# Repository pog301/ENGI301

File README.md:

# ENGI301 
Repository for ENGI301 course work.

This has four folders:

1) assignment_03
   A small section for one of the class asignments. 
3) project_01
   Folder containing the content for the first class project - see the README within this folder
4) project_02
   Folder containing the content for the second class project - see the README within this folder
6) python
   Any other python files not within project_01 developed in this course. 

Disclaimer: This includes student work developed as part of a course. As such, some components might be missing or do not work as desired, and the quality is that of someone learning this for the first time. Additionally, a lot of the code was developed as part of the course or facilitated by the work done in the course. Thus, I take no responsibility for the use of any file, code or any other part within this repository.

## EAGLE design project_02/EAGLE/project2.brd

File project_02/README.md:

# Project 2

The goal of project 2 was to create a Printed Circuit Board (PCB) Design for an Etch-a-Sketch. The PCB contains the following components in the front of the board:
1) SPI screen to draw on
2) x2 potentiometers (one for moving in the x direction and the other one for moving in the y direction) 
3) x2 buttons (one for changing the color you draw with and another one for reseting the game)
4) x3 LEDs (one red, one blue and one green to display the drawing color)

The PCB also has the following in the back:
1) USB Port
2) PocketBeagle

Additionally, the subfolder for this project ("project_02") within this repository contains the following subfolders:
1) A subfolder named "EAGLE" with the Library, Schematics and Layout needed to build the PCB
2) A subfolder named "MFG" containing all of the manufacturing files for the PCB
3) A subfolder named "docs" with any other documents submitted to the course as part of this project

Disclaimer: This is student work developed as part of a course. As such, some components might be missing and the quality is that of someone learning this for the first time. Additionally, a lot of the content was developed as part of the course or facilitated by the work done in the course. Thus, I take no responsibility for the use of any part of the project. Also, my professor helped me throughout the process, so I might not know the answers to some of the questions.

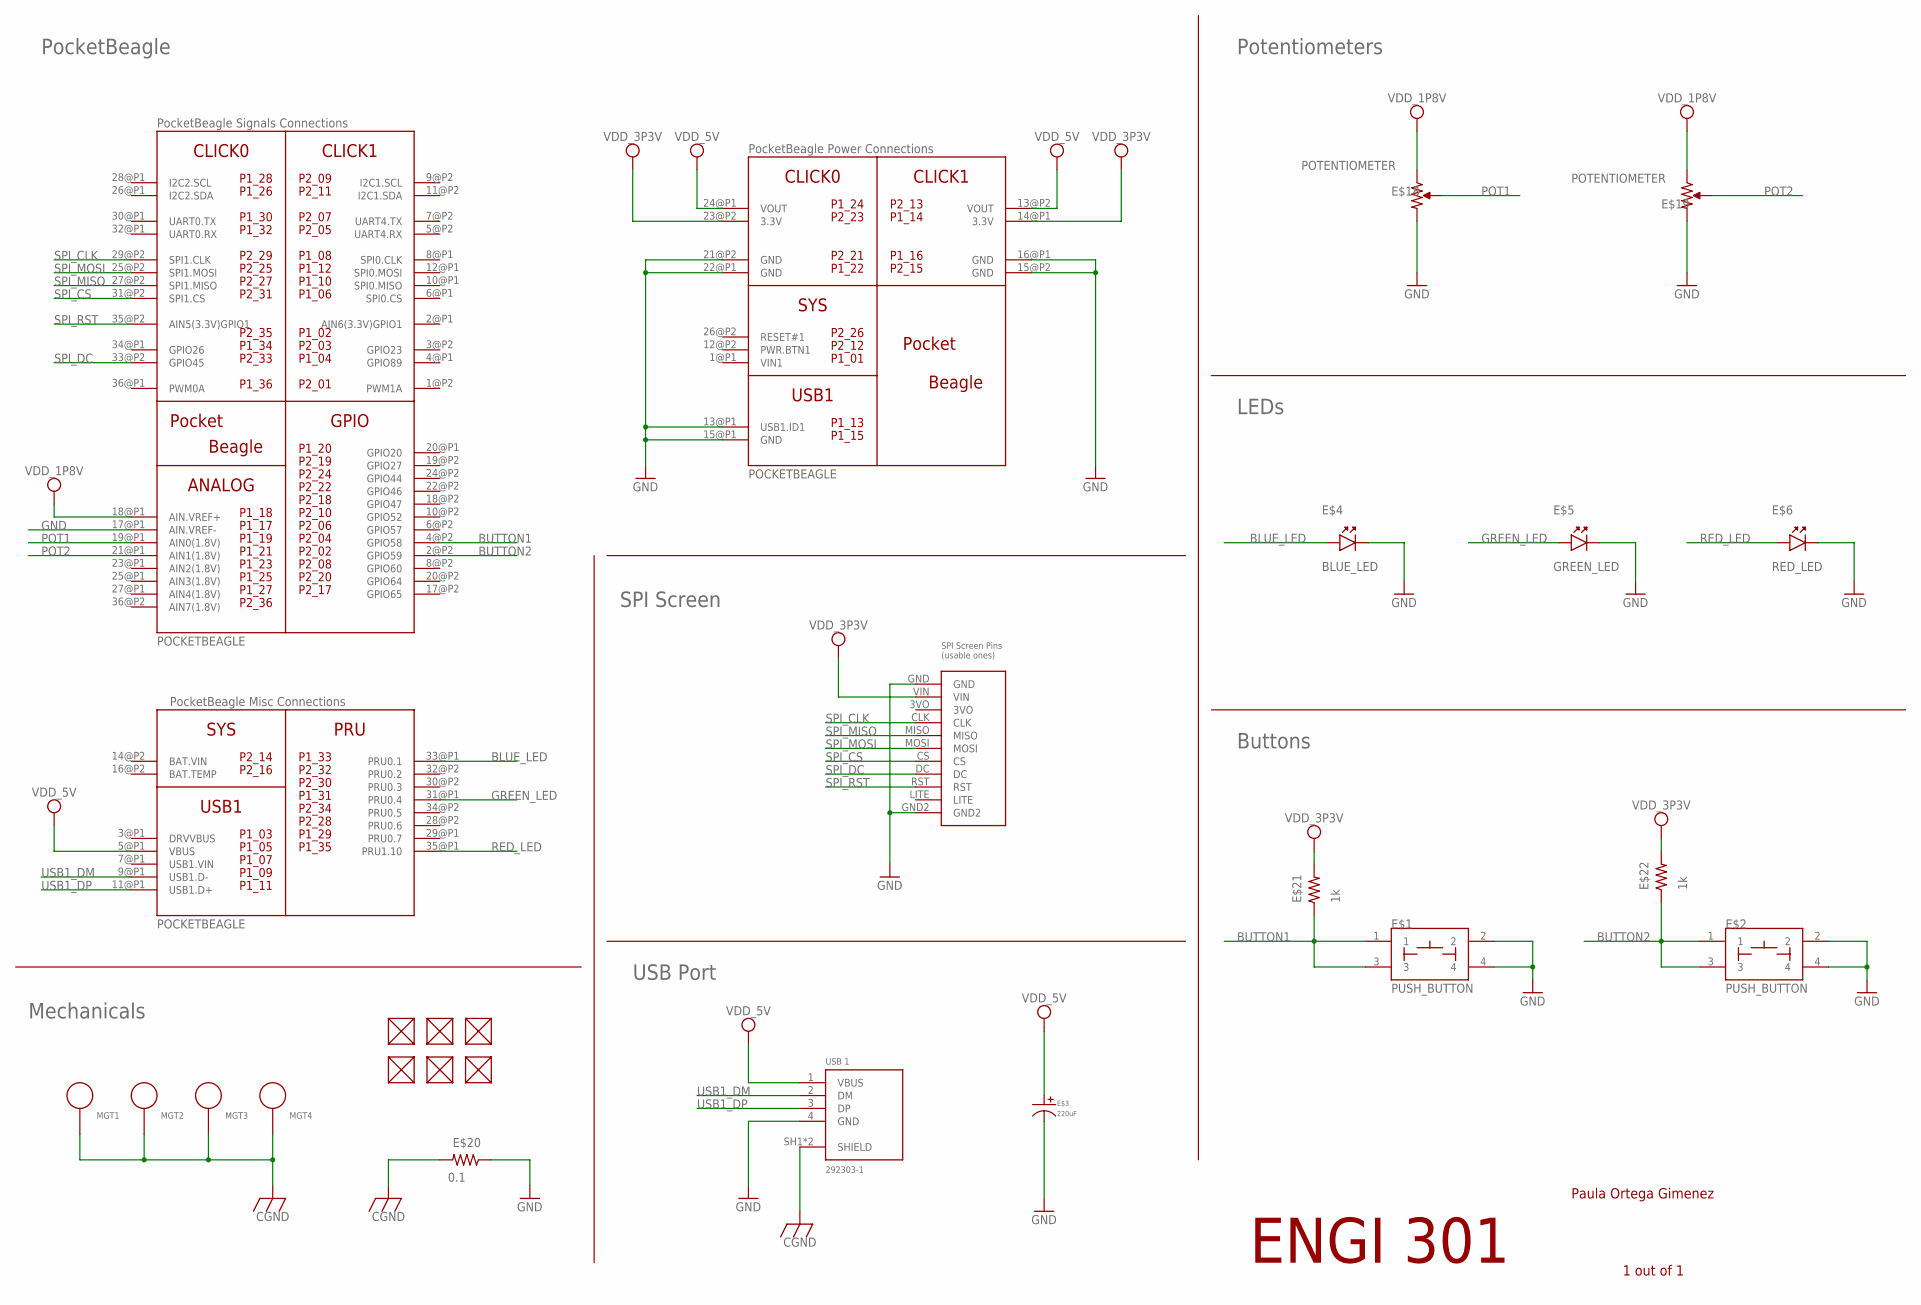
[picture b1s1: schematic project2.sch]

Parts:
E$1, E$2: PUSH_BUTTON; BUTTON_12.5MM
E$3: 220uF; CP10MM
E$4: BLUE_LED; EIA-STD
E$5: GREEN_LED; EIA-STD
E$6: RED_LED; EIA-STD
E$18, E$19: POTENTIOMETER; POT-PO90S
E$20: 0.1; R0805
E$21, E$22: 1k; R0805
E$24: 292303-1; TE_292303-1
FUD1, FUD2, FUD3, FUD4, FUD5, FUD6: FIDUCIAL; FIDUCIAL_40MIL
MGT1, MGT2, MGT3, MGT4: MOUNTING_HOLE
U1: SPI
U$1: POCKETBEAGLE

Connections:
BAT.VIN: U$1.14@P2 (BAT.VIN)
BLUE_LED: E$4.ANODE, U$1.33@P1 (PRU0.1)
BUTTON1: E$1.1, E$1.3, E$21.1, U$1.4@P2 (GPIO58)
BUTTON2: E$2.1, E$2.3, E$22.1, U$1.2@P2 (GPIO59)
CGND: E$20.2, E$24.SH1 (SHIELD), E$24.SH2 (SHIELD), MGT1.P$1, MGT2.P$1, MGT3.P$1, MGT4.P$1
GND: E$1.2, E$1.4, E$2.2, E$2.4, E$3.P$2, E$4.CATHODE, E$5.CATHODE, E$6.CATHODE, E$18.CW, E$19.CW, E$20.1, E$24.4 (GND), U1.GND, U1.GND2, U$1.13@P1 (USB1.ID1), U$1.15@P1 (GND), U$1.15@P2 (GND), U$1.16@P1 (GND), U$1.17@P1 (AIN.VREF-), U$1.21@P2 (GND), U$1.22@P1 (GND)
GREEN_LED: E$5.ANODE, U$1.31@P1 (PRU0.4)
POT1: E$18.S, U$1.19@P1 (AIN0(1.8V))
POT2: E$19.S, U$1.21@P1 (AIN1(1.8V))
RED_LED: E$6.ANODE, U$1.35@P1 (PRU1.10)
SPI_CLK: U1.CLK, U$1.29@P2 (SPI1.CLK)
SPI_CS: U1.CS, U$1.31@P2 (SPI1.CS)
SPI_DC: U1.DC, U$1.33@P2 (GPIO45)
SPI_MISO: U1.MISO, U$1.27@P2 (SPI1.MISO)
SPI_MOSI: U1.MOSI, U$1.25@P2 (SPI1.MOSI)
SPI_RST: U1.RST, U$1.35@P2 (AIN5(3.3V)GPIO1)
USB1_DM: E$24.2 (DM), U$1.9@P1 (USB1.D-)
USB1_DP: E$24.3 (DP), U$1.11@P1 (USB1.D+)
VDD_1P8V: E$18.CCW, E$19.CCW, U$1.18@P1 (AIN.VREF+)
VDD_3P3V: E$21.2, E$22.2, U1.VIN, U$1.14@P1 (3.3V), U$1.23@P2 (3.3V)
VDD_5V: E$3.P$1, E$24.1 (VBUS), U$1.5@P1 (VBUS), U$1.13@P2 (VOUT), U$1.24@P1 (VOUT)
VIN1: U$1.1@P1 (VIN1)

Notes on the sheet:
ENGI 301
Paula Ortega Gimenez
1 out of 1
Buttons
LEDs
Potentiometers
PocketBeagle
SPI Screen
USB Port
Mechanicals

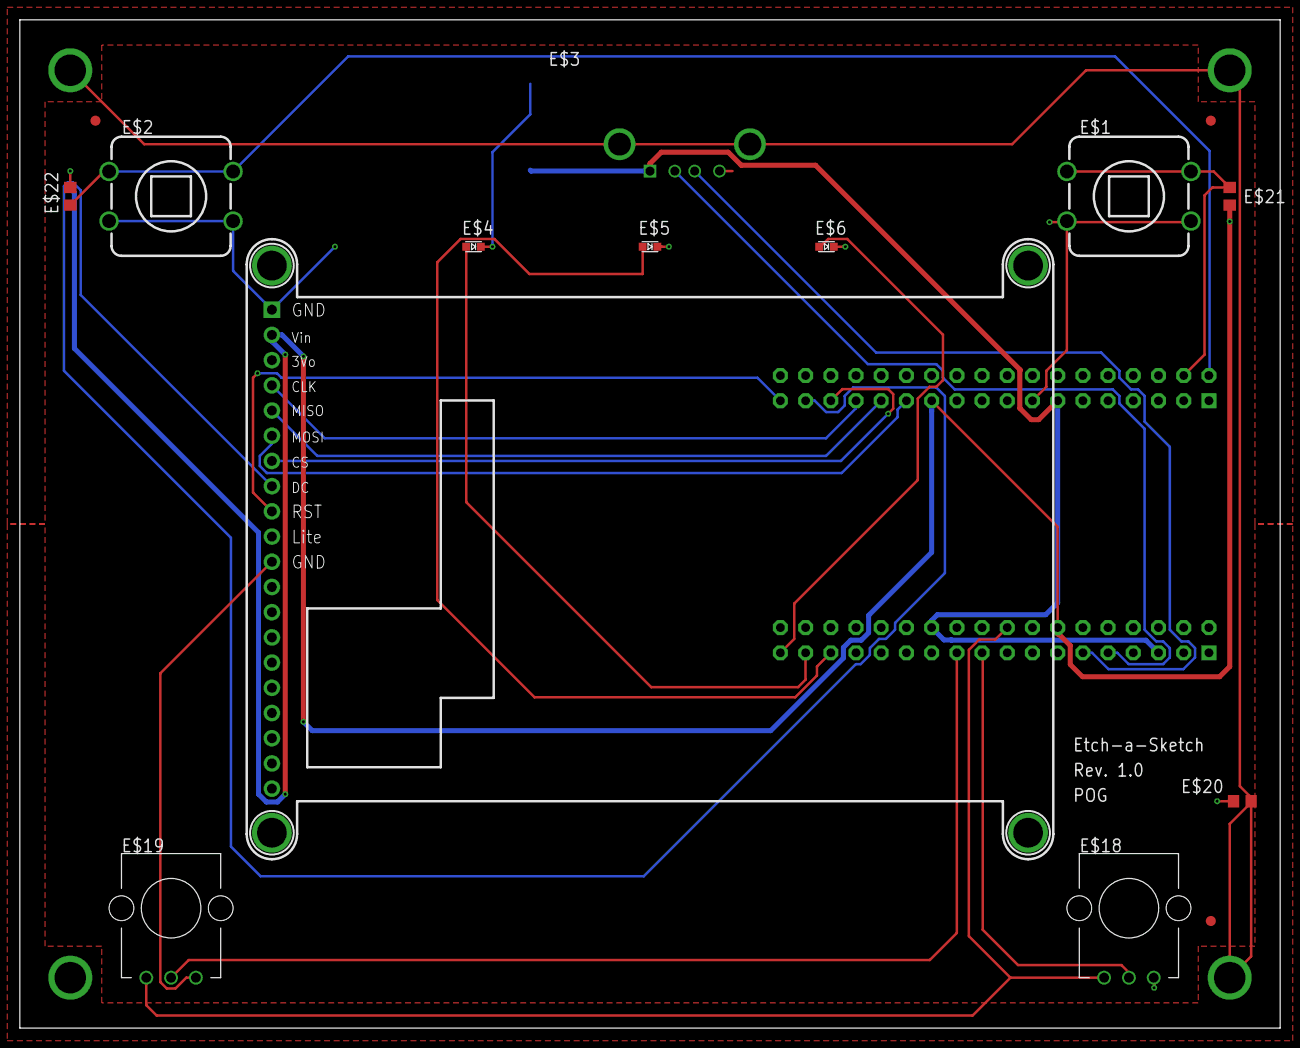
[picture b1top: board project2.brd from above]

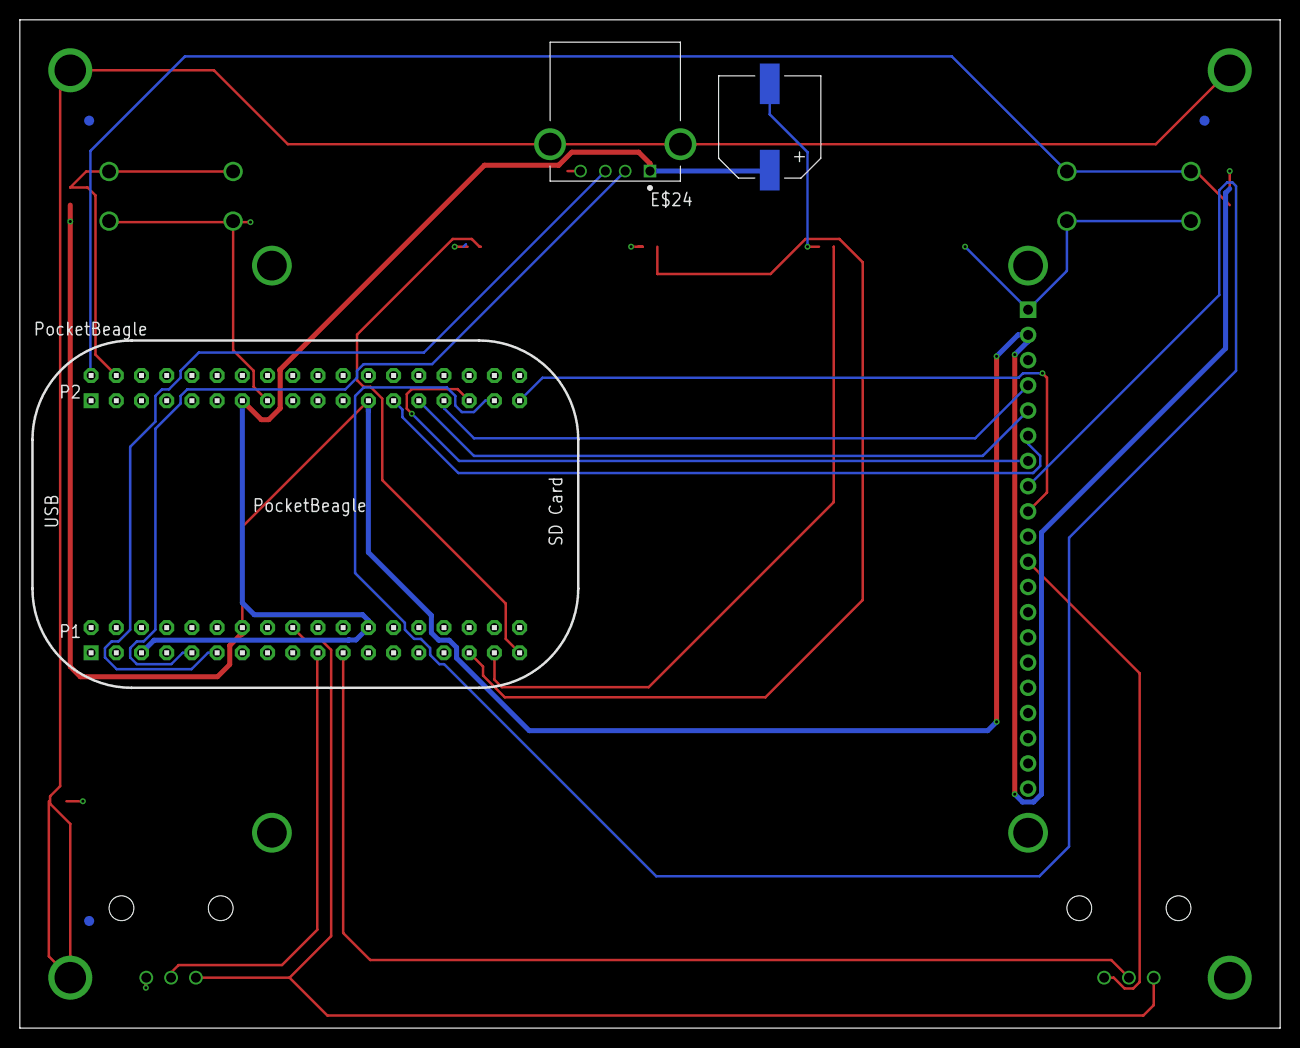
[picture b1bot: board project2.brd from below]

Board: 4 copper layers, 127.0 x 101.6 mm, 24 parts (6 on the bottom side), 20 nets.

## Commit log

2023-09-26 Create Proposal
2023-09-27 Checking in HW4
2023-10-02 Checking in HW3
2023-10-02 Updated simple_calc
2023-10-30 adding python files
2023-10-30 continued adding missing files from ENGI301
2023-11-08 commiting 11/7
2023-11-11 Adding files as of Nov. 11 12:24pm.
2023-11-14 Uploading files Nov. 13
2023-11-15 Commiting Nov 14 @8:58pm
2023-11-16 Commiting Nov 16
2023-11-20 Commiting Nov 19
2023-11-20 Commiting Nov. 22
2023-11-22 Commiting Nov. 22 after some changes in files
2023-11-22 Commiting Dec. 2
2023-12-04 Commiting Dec 3
2023-12-12 Create README.
2023-12-15 Rename project_02/Paula_Ortega_ENGI301_project_02_Slides.pptx to project_02/docs/Paula_Ortega_ENGI301_project_02_Slides.pptx
2023-12-15 Create RM temp
2023-12-16 Rename project_02/drill_1_16.xln to project_02/MFG/CAMOutputs/DrillFiles/drill_1_16.xln
2023-12-16 Rename project_02/copper_bottom_l4.gbr to project_02/MFG/CAMOutputs/GerberFiles/copper_bottom_l4.gbr
2023-12-16 Rename project_02/Copper Layer 2.png to project_02/MFG/Gerber_Screenshots/Copper Layer 2.png
